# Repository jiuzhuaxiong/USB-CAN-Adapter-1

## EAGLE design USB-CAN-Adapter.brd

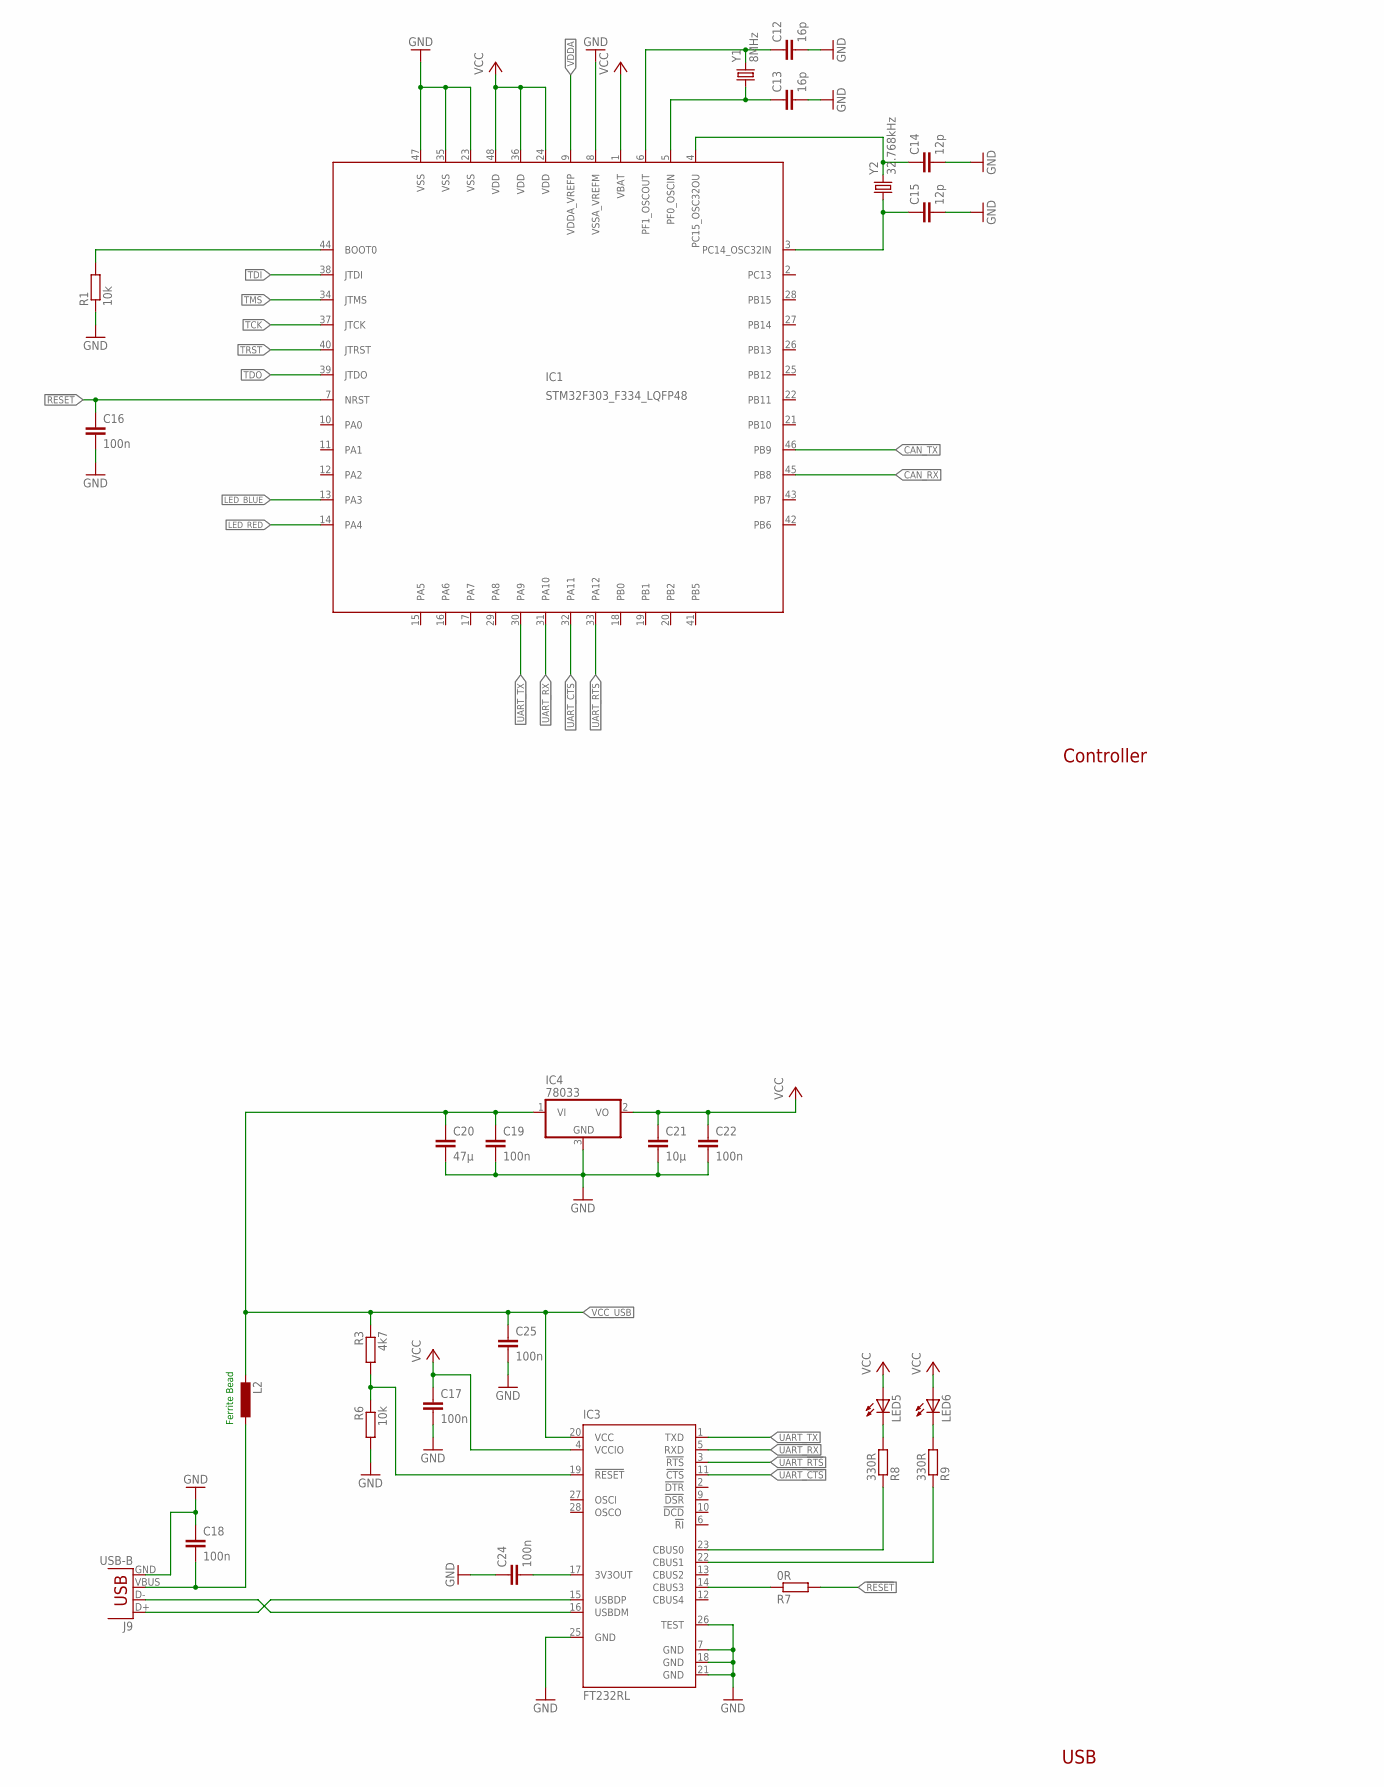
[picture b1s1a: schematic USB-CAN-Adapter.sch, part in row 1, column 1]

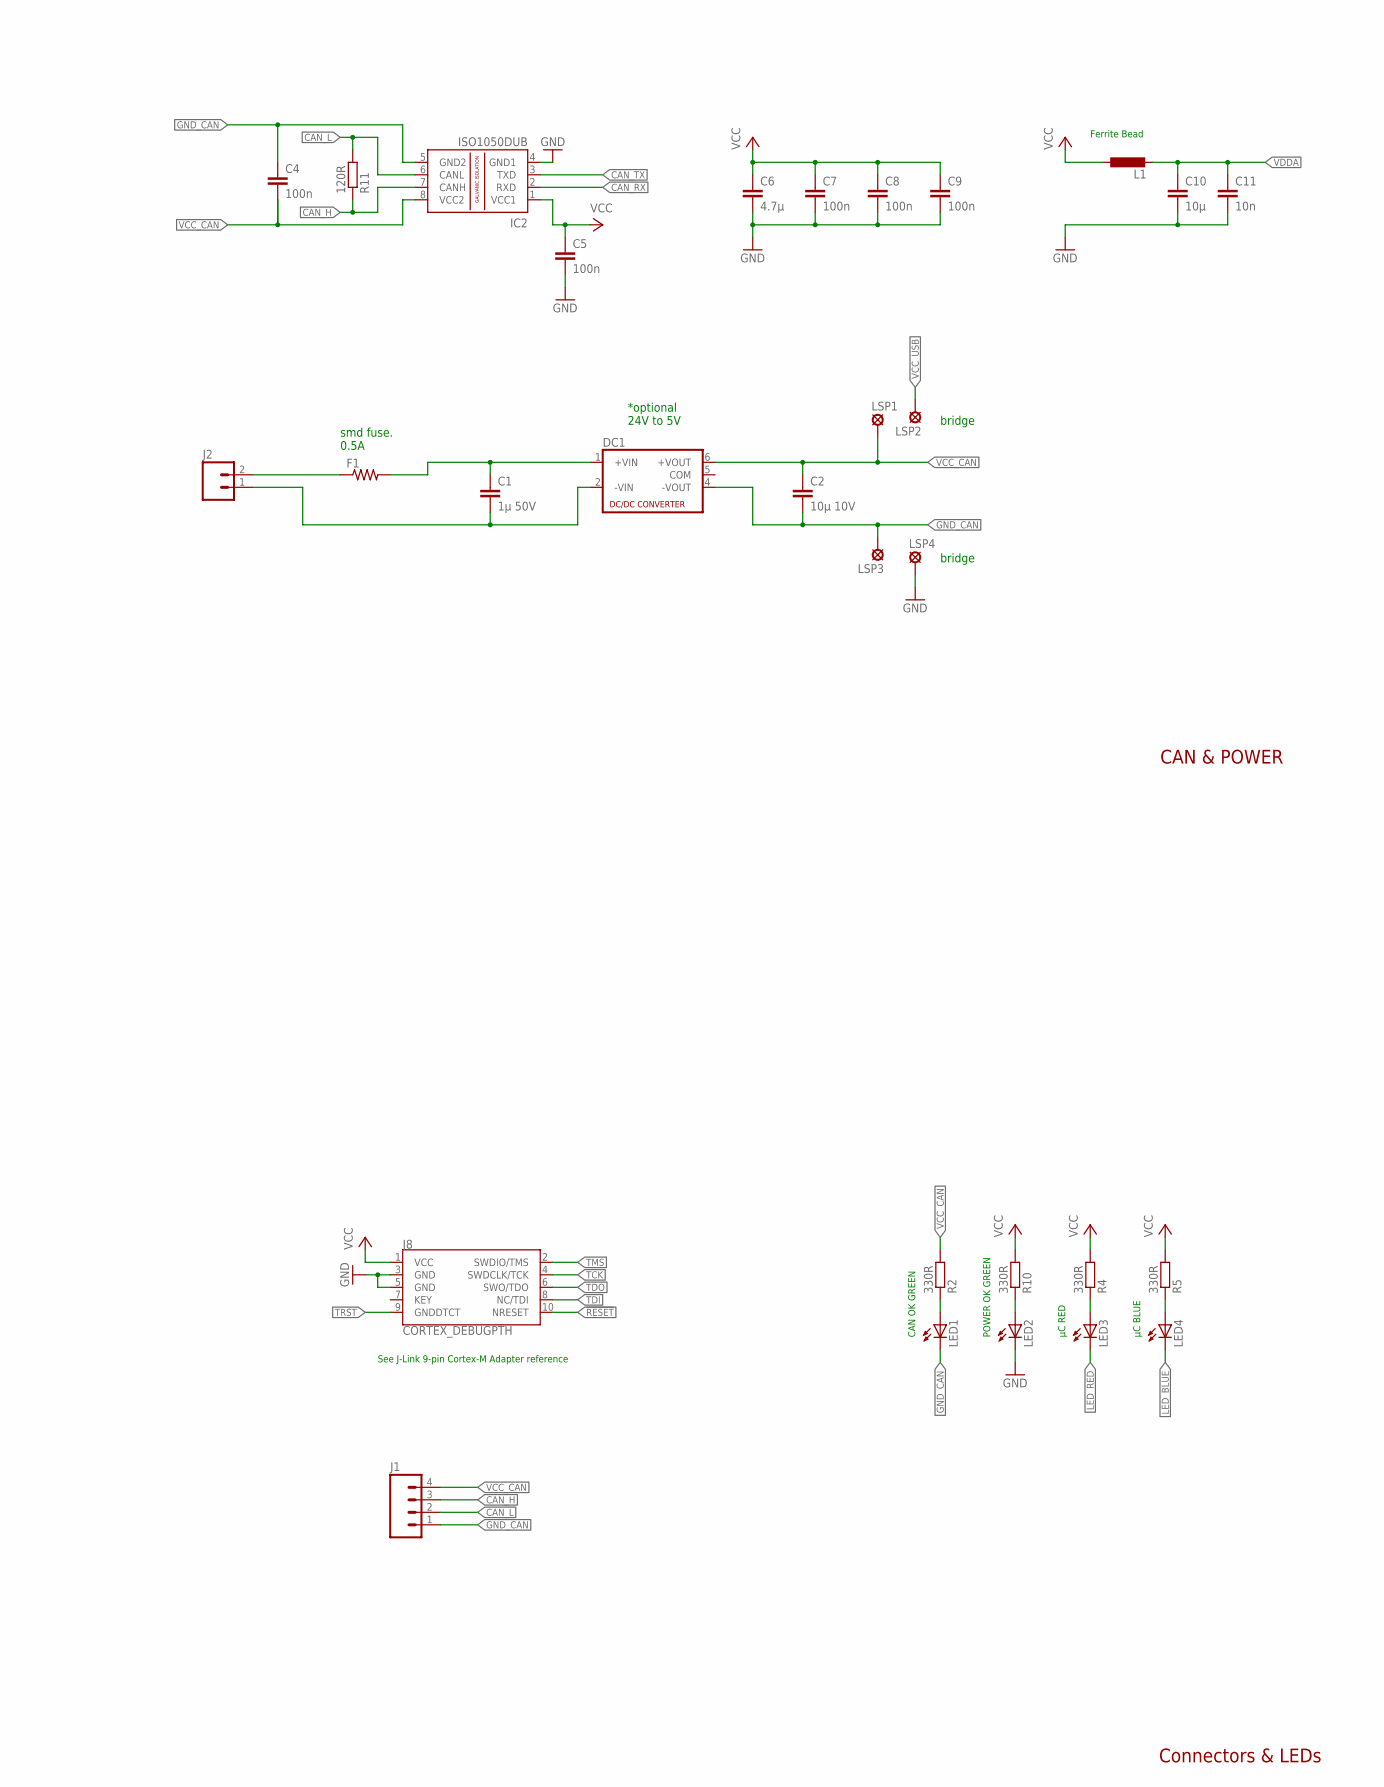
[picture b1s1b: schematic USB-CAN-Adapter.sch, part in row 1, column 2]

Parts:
C1: 1µ 50V; C0805
C2: 10µ 10V; C0805
C4, C5, C7, C8, C9, C16, C17, C18, C19, C22, C24, C25: 100n; C0805
C6: 4.7µ; C0805
C10, C21: 10µ; C0805
C11: 10n; C0805
C12, C13: 16p; C0805
C14, C15: 12p; C0805
C20: 47µ; C0805
DC1: NMA
F1: R-US_R0805; R0805
IC1: STM32F303_F334_LQFP48; LQFP48_PACKAGE
IC2: ISO1050DUB; DUB-R-PDSO-G8
IC3: FT232RL; SSOP28
IC4: 78033; TO252
J1: M04SCREW; SCREWTERMINAL-3.5MM-4
J2: M023.5MM; SCREWTERMINAL-3.5MM-2
J8: CORTEX_DEBUGPTH; 2X5-PTH-1.27MM
J9: USB-B; USB-B-PTH
L1, L2: L-EUL2012C; L2012C
LED1, LED2, LED3, LED4, LED5, LED6: LEDCHIP-LED0805; CHIP-LED0805
LSP1, LSP2, LSP3, LSP4: LSP13
R1, R6: 10k; R0805
R2, R4, R5, R8, R9, R10: 330R; R0805
R3: 4k7; R0805
R7: 0R; R0805
R11: 120R; R0805
Y1: 8MHz; CRYSTAL-SMD-5X3
Y2: 32.768kHz; CRYSTAL-SMD-3.2X1.5MM

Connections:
!RESET: C16.1, IC1.7 (NRST), J8.10 (NRESET), R7.2
CAN_H: IC2.7 (CANH), J1.3, R11.1
CAN_L: IC2.6 (CANL), J1.2, R11.2
CAN_RX: IC1.45 (PB8), IC2.2 (RXD)
CAN_TX: IC1.46 (PB9), IC2.3 (TXD)
GND: C5.2, C6.2, C7.2, C8.2, C9.2, C10.2, C11.2, C12.2, C13.2, C14.2, C15.2, C16.2, C17.2, C18.1, C19.2, C20.2, C21.2, C22.2, C24.1, C25.2, IC1.8 (VSSA_VREFM), IC1.23 (VSS), IC1.35 (VSS), IC1.47 (VSS), IC2.4 (GND1), IC3.7 (GND), IC3.18 (GND), IC3.21 (GND), IC3.25 (GND), IC3.26 (TEST), IC4.3 (GND), J8.3 (GND), J8.5 (GND), J9.GND, LED2.C, LSP4.MP, R1.1, R6.2
GND_CAN: C2.2, C4.1, DC1.4 (-VOUT), IC2.5 (GND2), J1.1, LED1.C, LSP3.MP
LED_BLUE: IC1.13 (PA3), LED4.C
LED_RED: IC1.14 (PA4), LED3.C
unnamed: F1.1, J2.2
unnamed: C1.1, DC1.1 (+VIN), F1.2
unnamed: C1.2, DC1.2 (-VIN), J2.1
unnamed: IC1.44 (BOOT0), R1.2
unnamed: LED1.A, R2.1
unnamed: LED2.A, R10.1
unnamed: C12.1, IC1.6 (PF1_OSCOUT), Y1.3 (2)
unnamed: C13.1, IC1.5 (PF0_OSCIN), Y1.1
unnamed: LED3.A, R4.1
unnamed: LED4.A, R5.1
unnamed: C14.1, IC1.4 (PC15_OSC32OU), Y2.P$2 (2)
unnamed: C15.1, IC1.3 (PC14_OSC32IN), Y2.P$1 (1)
unnamed: IC3.16 (USBDM), J9.D-
unnamed: IC3.15 (USBDP), J9.D+
unnamed: IC3.19 (!RESET), R3.2, R6.1
unnamed: C18.2, J9.VBUS, L2.1
unnamed: IC3.14 (CBUS3), R7.1
unnamed: C24.2, IC3.17 (3V3OUT)
unnamed: IC3.23 (CBUS0), R8.1
unnamed: IC3.22 (CBUS1), R9.1
unnamed: LED5.C, R8.2
unnamed: LED6.C, R9.2
TCK: IC1.37 (JTCK), J8.4 (SWDCLK/TCK)
TDI: IC1.38 (JTDI), J8.8 (NC/TDI)
TDO: IC1.39 (JTDO), J8.6 (SWO/TDO)
TMS: IC1.34 (JTMS), J8.2 (SWDIO/TMS)
TRST: IC1.40 (JTRST), J8.9 (GNDDTCT)
UART_!CTS: IC1.32 (PA11), IC3.11 (!CTS)
UART_!RTS: IC1.33 (PA12), IC3.3 (!RTS)
UART_RX: IC1.31 (PA10), IC3.5 (RXD)
UART_TX: IC1.30 (PA9), IC3.1 (TXD)
VCC: C5.1, C6.1, C7.1, C8.1, C9.1, C17.1, C21.1, C22.1, IC1.1 (VBAT), IC1.24 (VDD), IC1.36 (VDD), IC1.48 (VDD), IC2.1 (VCC1), IC3.4 (VCCIO), IC4.2 (VO), J8.1 (VCC), L1.1, LED5.A, LED6.A, R4.2, R5.2, R10.2
VCC_CAN: C2.1, C4.2, DC1.6 (+VOUT), IC2.8 (VCC2), J1.4, LSP1.MP, R2.2
VCC_USB: C19.1, C20.1, C25.1, IC3.20 (VCC), IC4.1 (VI), L2.2, LSP2.MP, R3.1
VDDA: C10.1, C11.1, IC1.9 (VDDA_VREFP), L1.2

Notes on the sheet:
smd fuse. 0.5A
Ferrite Bead
CAN OK GREEN
POWER OK GREEN
µC RED
µC BLUE
See J-Link 9-pin Cortex-M Adapter reference
*optional 24V to 5V
USB
Connectors & LEDs
CAN & POWER
Controller
bridge

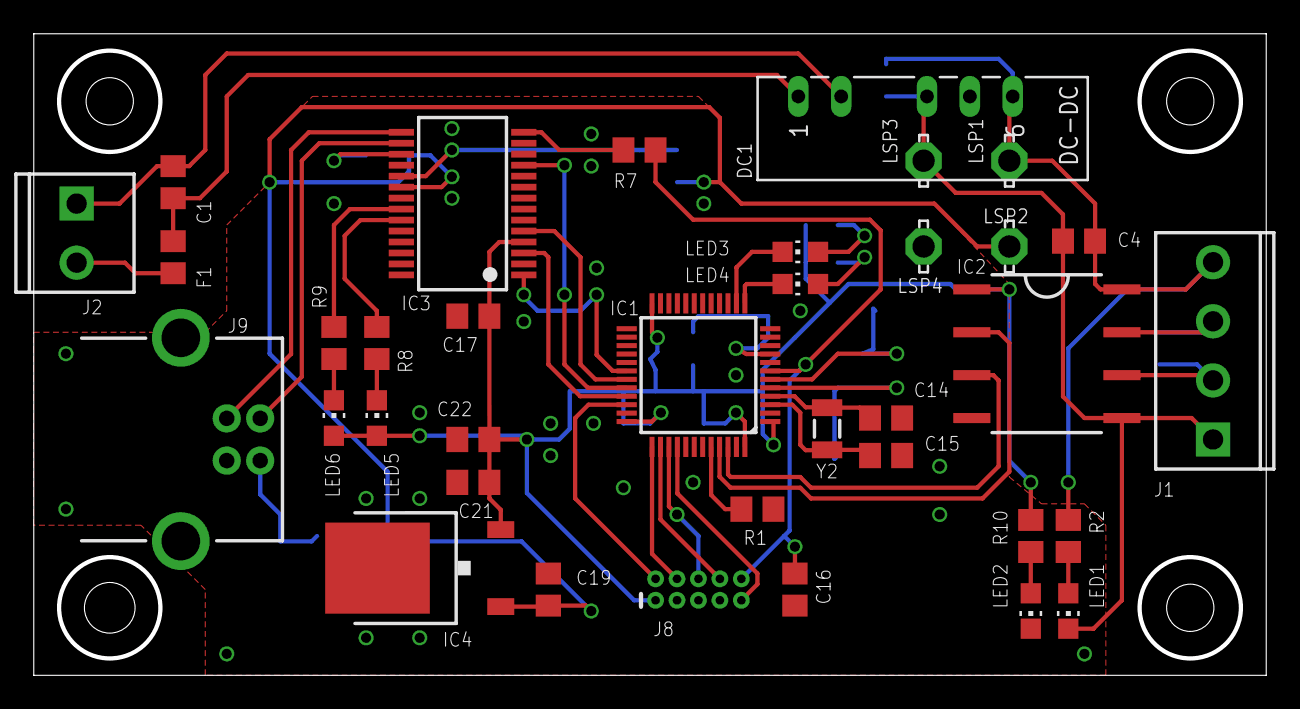
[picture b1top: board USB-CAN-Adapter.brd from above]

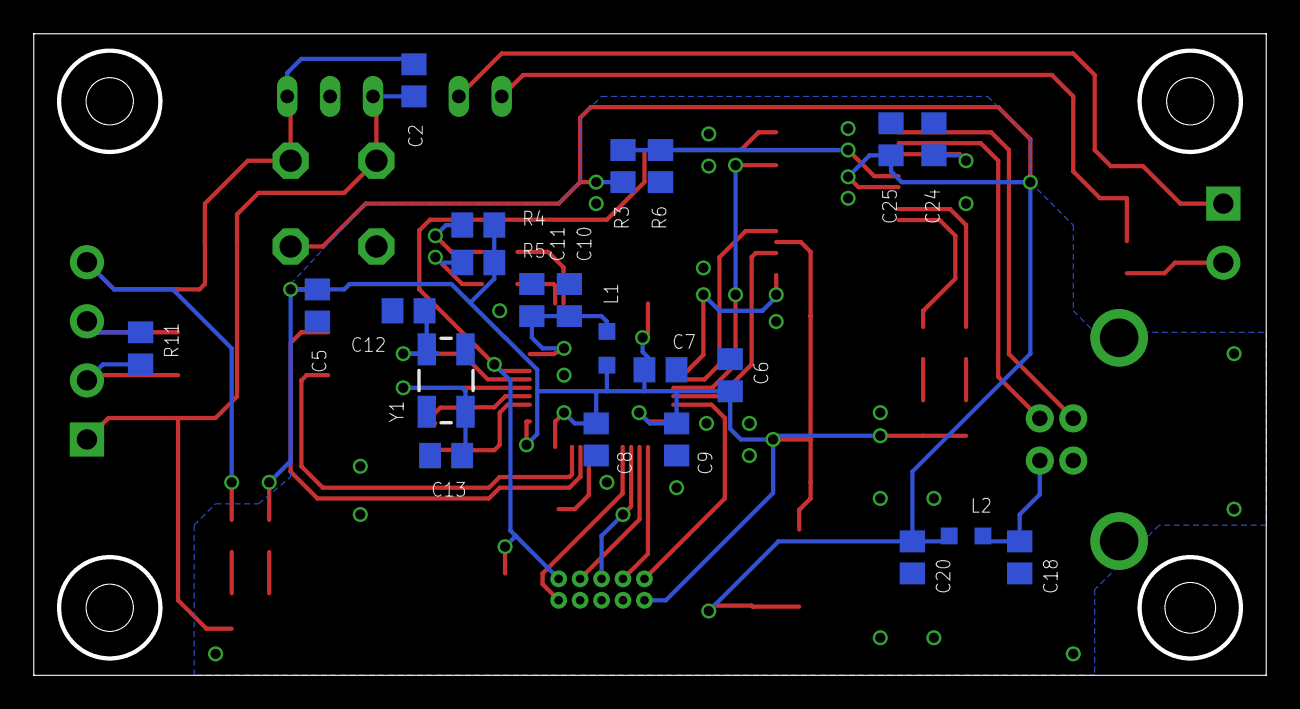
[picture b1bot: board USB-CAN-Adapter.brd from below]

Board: 2 copper layers, 72.7 x 37.7 mm, 58 parts (22 on the bottom side), 44 nets.

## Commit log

2016-11-17 initial schematic
2016-11-27 board initial

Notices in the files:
parts and their libraries:
SparkFun-Connectors: Licensing: Creative Commons ShareAlike 4.0 International - https://creativecommons.org/licenses/by-sa/4.0
